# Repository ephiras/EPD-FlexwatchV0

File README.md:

# The Inkwell Watch (A curved eink watch)

previously the flexwatch.

A simple, low stress smartwatch built around a 2.9 inch e ink display, a custom PCB, and a lot of improvised problem solving. This repository contains the Arduino code and the Eagle hardware files for the current working version.

The goal is a comfortable watch that is easy on the eyes, lasts a long time on a charge, and does not behave like a tiny phone.

---

## What is in this repository

### code
Arduino sketches for the current version.  
Bluetooth and microphone support are not implemented yet, but the hardware is ready.

### hardware
Eagle schematic and PCB layout for the custom flex board used in the build.

---

## Current features

- 2.9 inch e ink display  
- Seeed Studio nRF52840 Sense  
- IMU support  
- Basic watch interface  
- Low power modes  
- Custom flex PCB  
- Ruler based rigid frame  

---

## Planned features

- Bluetooth  
- Microphone  
- GPS (new layout needed)  
- Heart rate sensor  
- UV sensor  
- Rigid flex PCB  
- Improved sleep modes  
- RTC backup battery  

---

# The Zephyr Migration
I’ve started migrating the firmware for the e‑ink smartwatch from the Arduino environment to Zephyr RTOS. This is a significant step forward for the project and sets up a much more robust foundation for future development.

## Why the migration
- Better power management: Zephyr gives fine‑grained control over sleep states, peripherals, and scheduling, which is essential for a low‑power wearable running on a small battery.
- Native nRF52840 support: Zephyr’s Nordic integration is far deeper than Arduino’s, with first‑class drivers, BLE stack support, and stable APIs.
- Modular architecture: The RTOS structure makes it easier to separate display handling, sensors, BLE, and UI logic into clean, maintainable modules.
- Scalability: As the watch grows beyond a simple prototype, Arduino’s abstractions become limiting. Zephyr provides a long‑term path for more complex features.

---

## Notes
This is a work in progress.  
The hardware files match the version shown in the Instructables build.  https://www.instructables.com/Building-a-Lightweight-Curved-EInk-Smartwatch/
Expect changes as the design evolves.

if you want to, please join the discord
https://discord.gg/58VtJPHzf

## License

MIT License.  
Feel free to use, modify, and build on this project.

Please reach out or credit me if you do use any of my schematics/ pcb layout. I would really appreciate it! would also be great to see what you come up with.

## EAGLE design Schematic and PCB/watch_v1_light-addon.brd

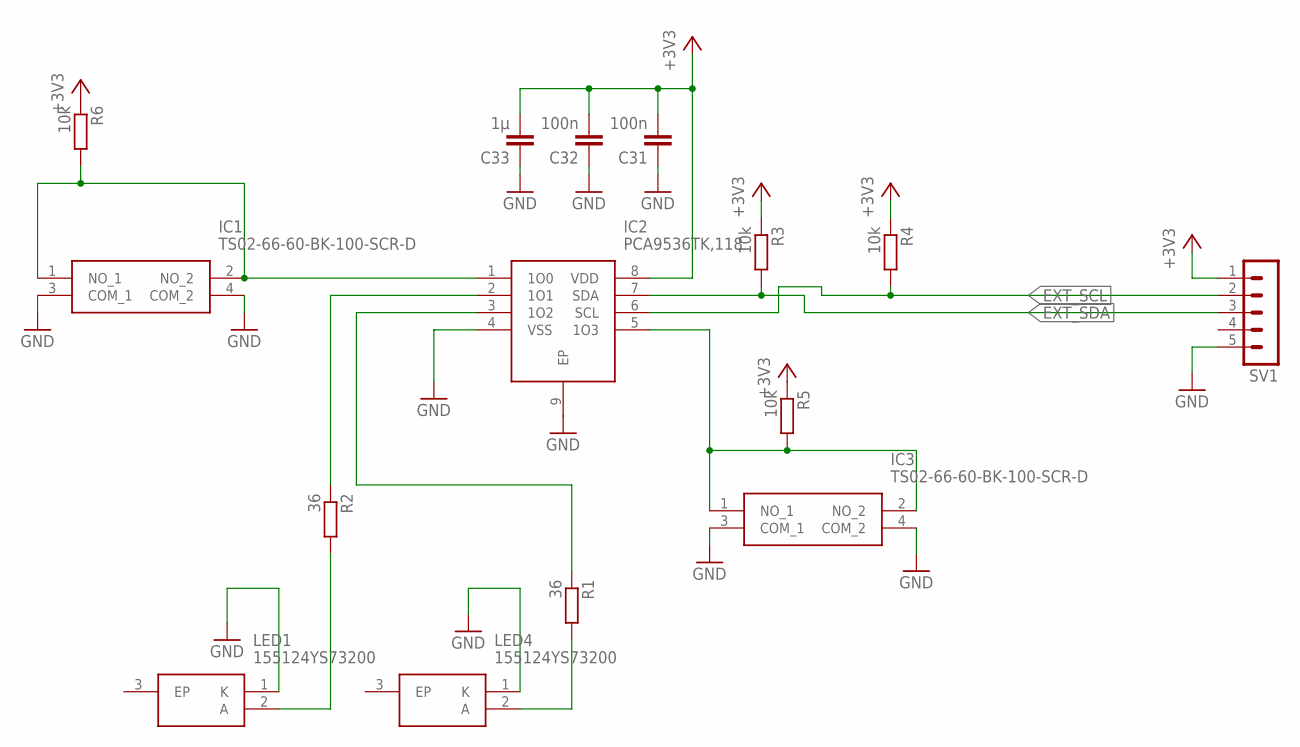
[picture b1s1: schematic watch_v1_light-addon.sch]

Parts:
C31, C32: 100n; C0402_S
C33: 1µ; C0402_S
IC1, IC3: TS02-66-60-BK-100-SCR-D; TS026660BK100SCRD
IC2: PCA9536TK,118; SON50P300X300X100-9N
LED1, LED4: 155124YS73200
R1, R2: 36; R0402
R3, R4, R5, R6: 10k; R0402
SV1: MA05-1

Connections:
+3V3: C31.P$2 (2), C32.P$2 (2), C33.P$2 (2), IC2.8 (VDD), R3.1, R4.1, R5.1, R6.1, SV1.1
EXT_SCL: IC2.6 (SCL), R4.2, SV1.2
EXT_SDA: IC2.7 (SDA), R3.2, SV1.3
GND: C31.P$1 (1), C32.P$1 (1), C33.P$1 (1), IC1.3 (COM_1), IC1.4 (COM_2), IC2.4 (VSS), IC2.9 (EP), IC3.3 (COM_1), IC3.4 (COM_2), LED1.1 (K), LED4.1 (K), SV1.5
unnamed: IC1.1 (NO_1), IC1.2 (NO_2), IC2.1 (1O0), R6.2
unnamed: IC2.2 (1O1), R2.1
unnamed: LED4.2 (A), R1.2
unnamed: LED1.2 (A), R2.2
unnamed: IC2.3 (1O2), R1.1
unnamed: IC2.5 (1O3), IC3.1 (NO_1), IC3.2 (NO_2), R5.2

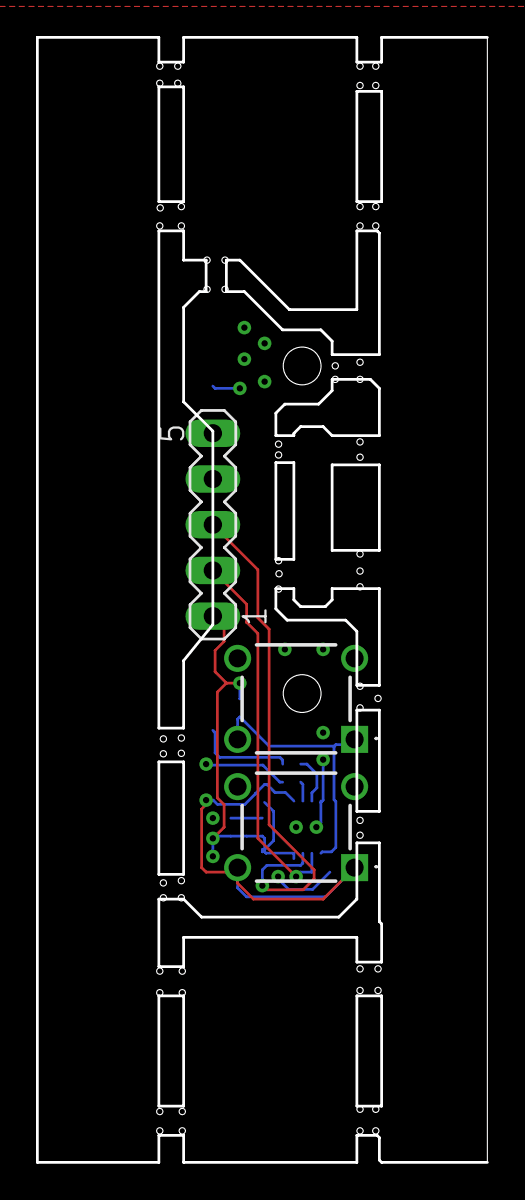
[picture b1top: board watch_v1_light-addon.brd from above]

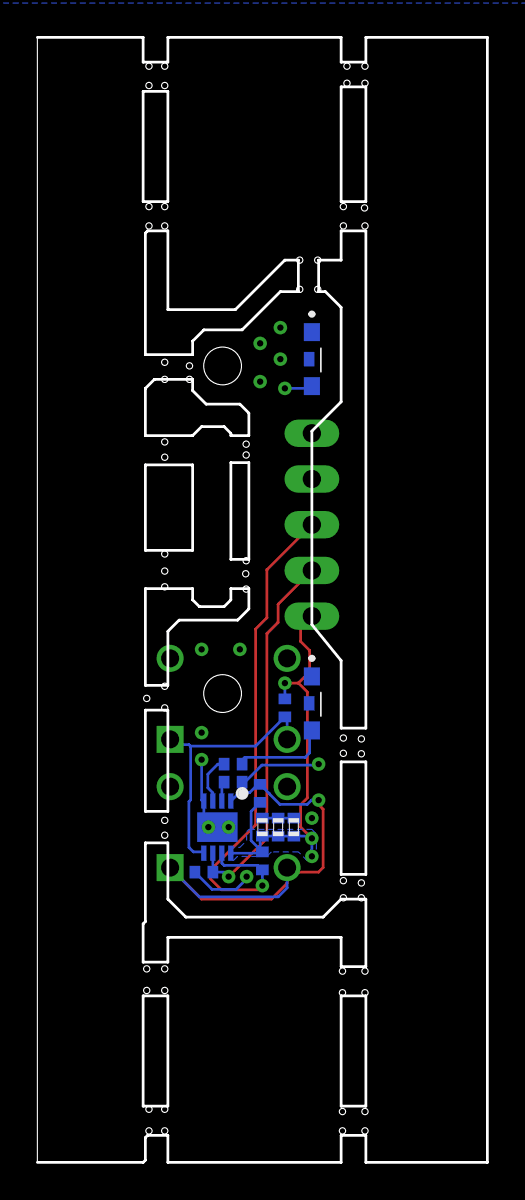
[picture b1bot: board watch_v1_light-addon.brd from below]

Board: 4 copper layers, 25.0 x 62.5 mm, 15 parts (12 on the bottom side), 10 nets.

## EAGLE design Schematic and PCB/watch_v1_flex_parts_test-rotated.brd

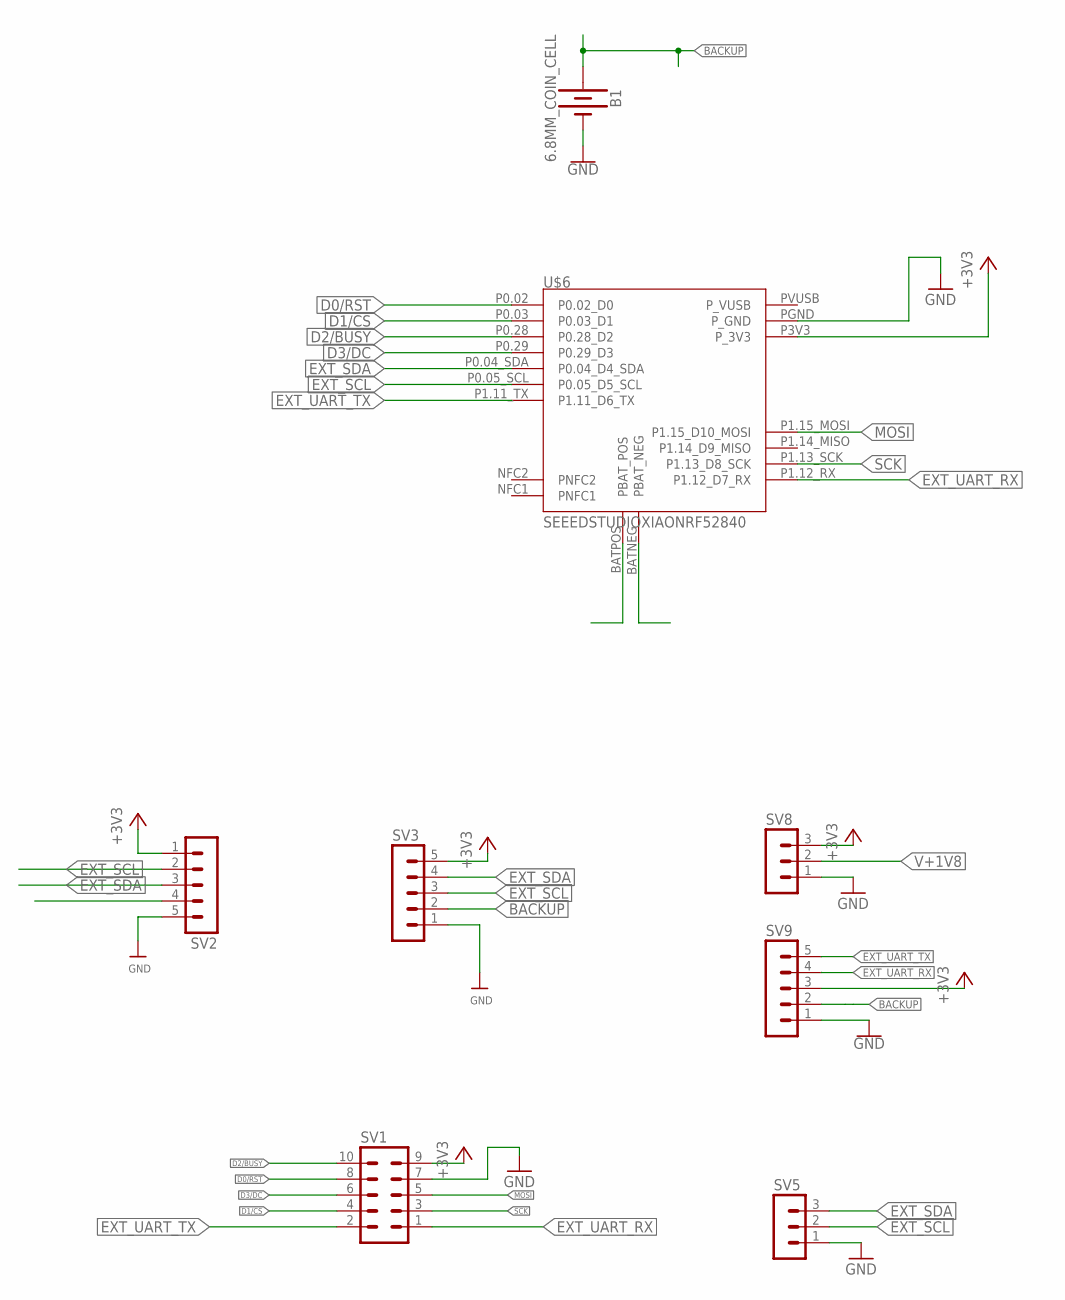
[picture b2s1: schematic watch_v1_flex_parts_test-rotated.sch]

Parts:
B1: 6.8MM_COIN_CELL; ML414H_IV01E
SV1: MA05-2
SV2, SV3, SV9: MA05-1
SV5, SV8: MA03-1
U$6: SEEEDSTUDIOXIAONRF52840

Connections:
+3V3: SV1.9, SV2.1, SV3.5, SV8.3, SV9.3, U$6.P3V3 (P_3V3)
BACKUP: B1.+, SV3.2, SV9.2
D0/RST: SV1.8, U$6.P0.02 (P0.02_D0)
D1/CS: SV1.4, U$6.P0.03 (P0.03_D1)
D2/BUSY: SV1.10, U$6.P0.28 (P0.28_D2)
D3/DC: SV1.6, U$6.P0.29 (P0.29_D3)
EXT_SCL: SV2.2, SV3.3, SV5.2, U$6.P0.05_SCL (P0.05_D5_SCL)
EXT_SDA: SV2.3, SV3.4, SV5.3, U$6.P0.04_SDA (P0.04_D4_SDA)
EXT_UART_RX: SV1.1, SV9.4, U$6.P1.12_RX (P1.12_D7_RX)
EXT_UART_TX: SV1.2, SV9.5, U$6.P1.11_TX (P1.11_D6_TX)
GND: B1.-, SV1.7, SV2.5, SV3.1, SV5.1, SV8.1, SV9.1, U$6.PGND (P_GND)
MOSI: SV1.5, U$6.P1.15_MOSI (P1.15_D10_MOSI)
SCK: SV1.3, U$6.P1.13_SCK (P1.13_D8_SCK)
V+1V8: SV8.2

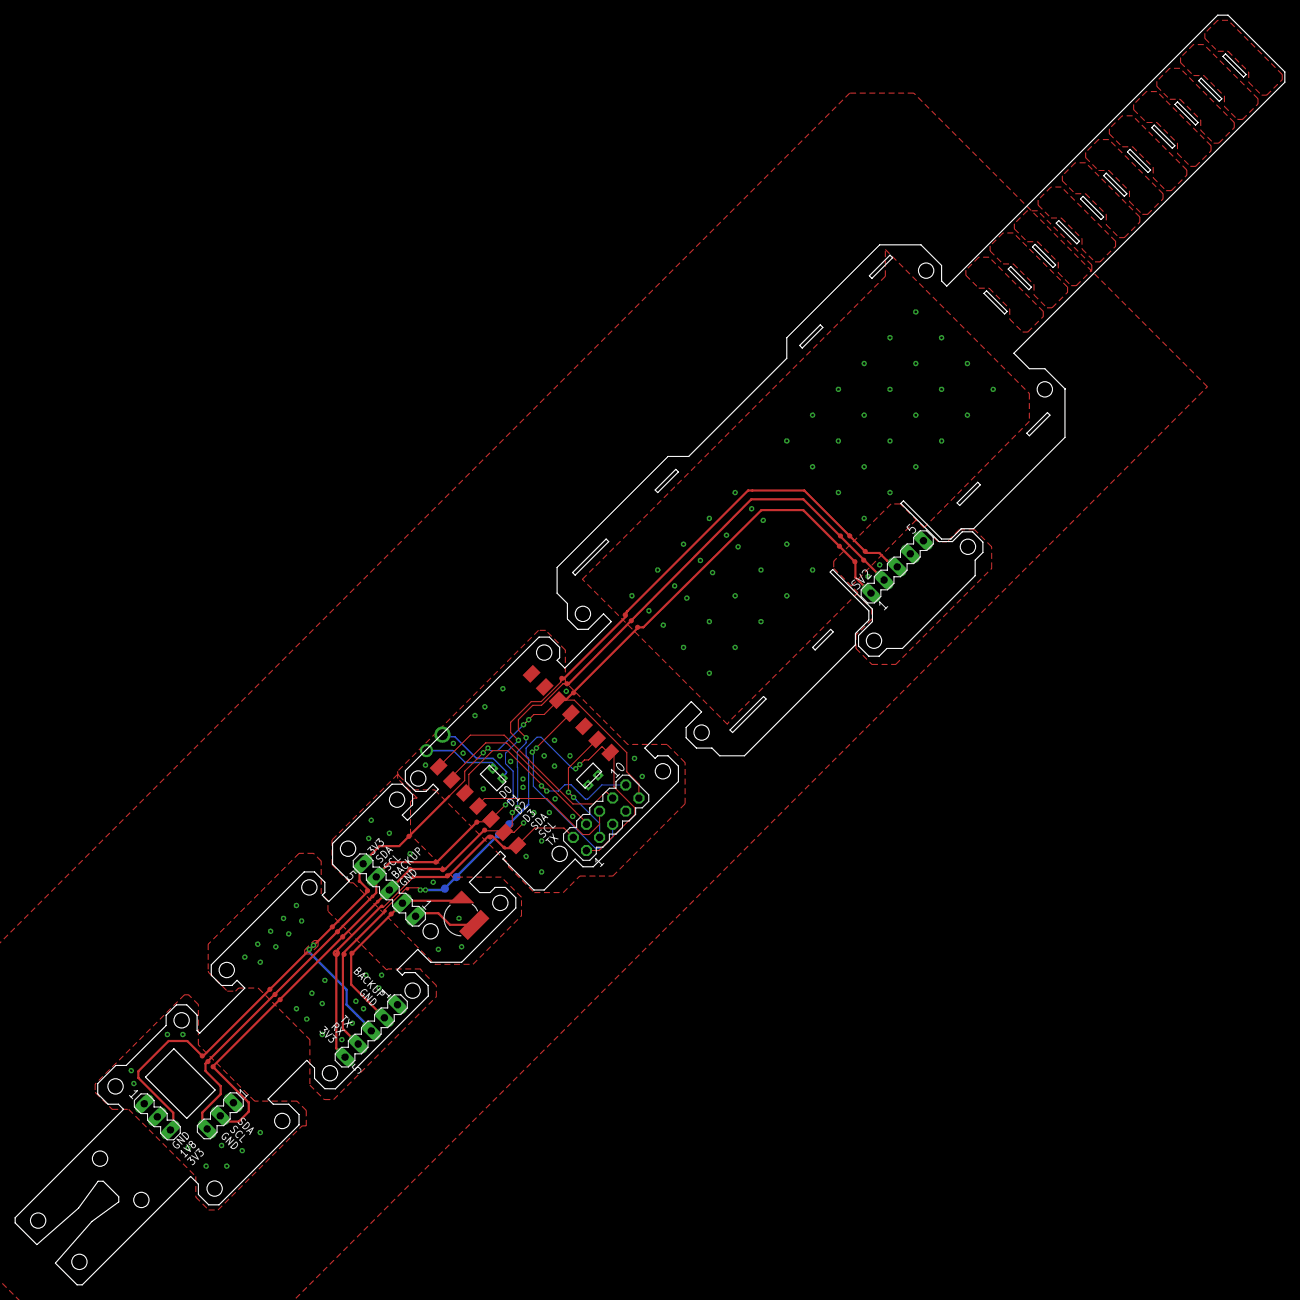
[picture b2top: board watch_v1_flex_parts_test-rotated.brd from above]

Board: 2 copper layers, 173.9 x 173.9 mm, 8 parts (0 on the bottom side), 13 nets.

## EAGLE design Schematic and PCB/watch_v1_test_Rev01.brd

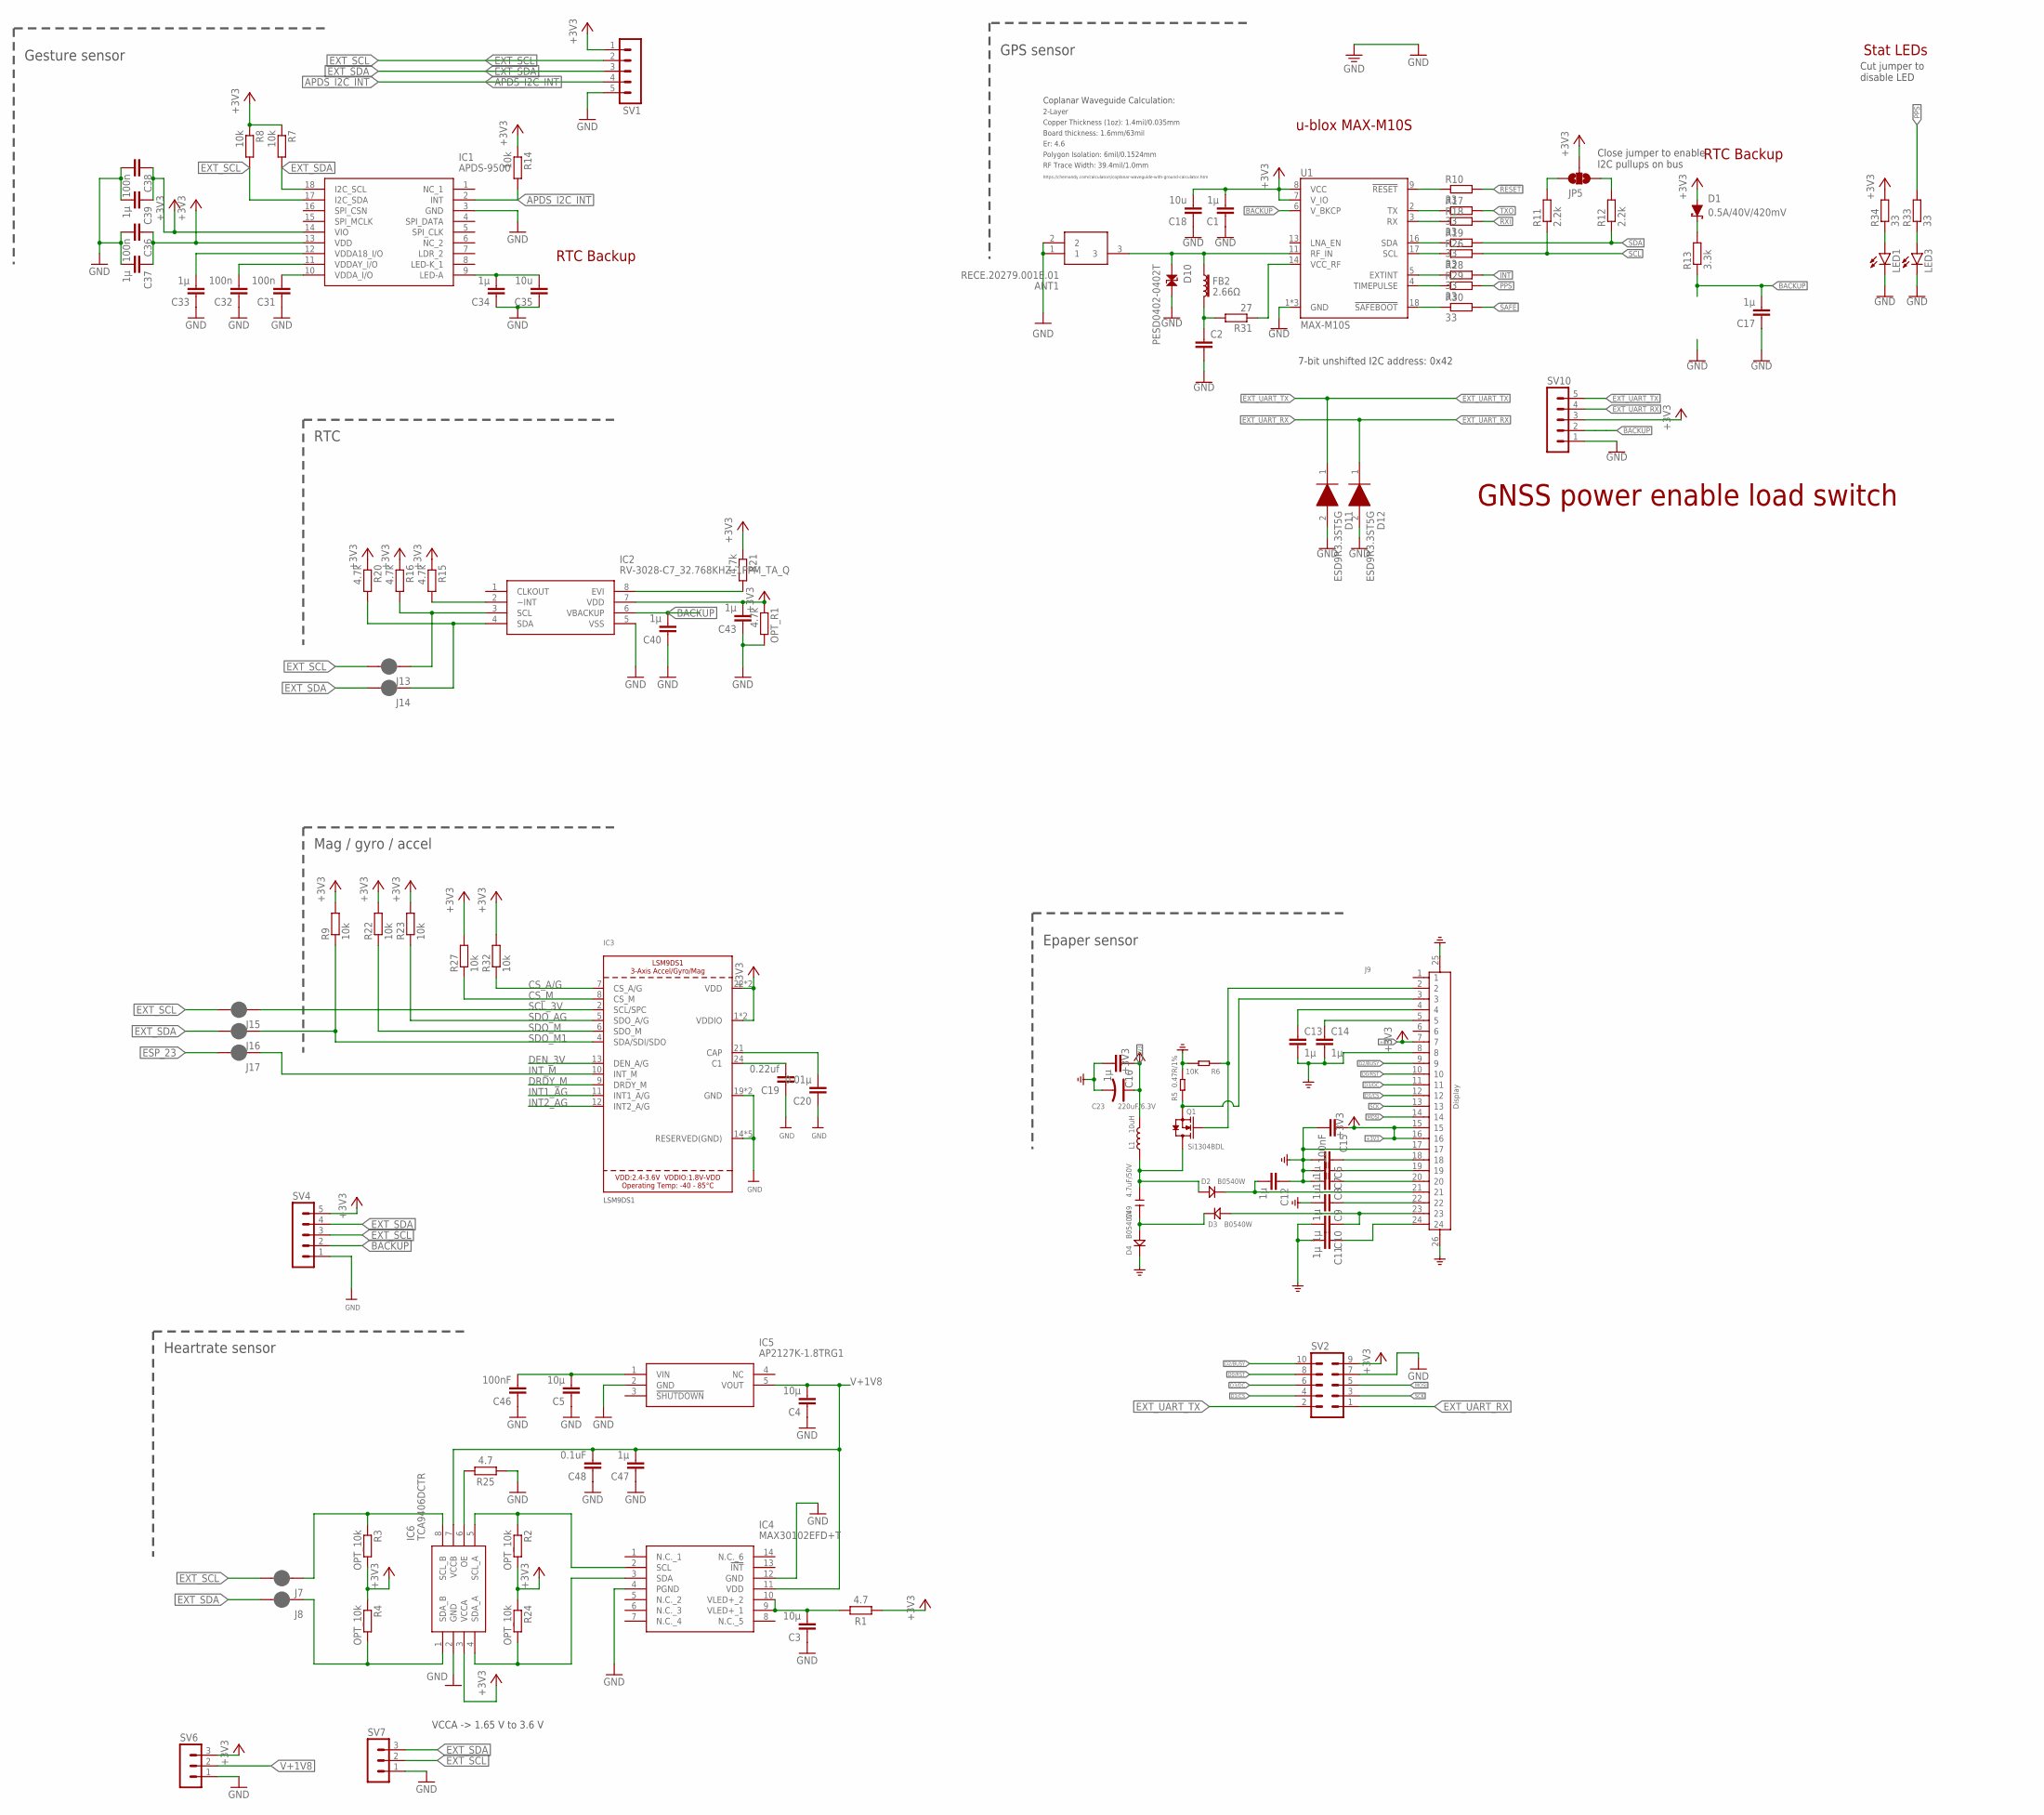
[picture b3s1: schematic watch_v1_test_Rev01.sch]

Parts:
ANT1: RECE.20279.001E.01
C1, C6, C7, C8, C9, C10, C11, C12, C13, C14, C16, C17, C33, C34, C37, C39, C40, C43, C47: 1µ; C0402_S
C2: 47pF; 0402-TIGHT
C3, C4, C5: 10µ; C0402_S
C15, C46: 100nF; C0402_S
C18, C35: 10u; C0402_S
C19: 0.22uf; C0402_S
C20: 0.01µ; C0402_S
C23: 220uF/6.3V; AVX-B
C31, C32, C36, C38: 100n; C0402_S
C48: 0.1uF; C0402_S
C49: 4.7uF/50V; C1206
D1: 0.5A/40V/420mV; SOD-323
D2, D3, D4: B0540W; SOD-323
D10: PESD0402-0402T; 0402-TIGHT
D11, D12: ESD9R3.3ST5G; SODFL1006X40N
FB2: 2.66Ω; 0402-TIGHT
IC1: APDS-9500; APDS9500
IC2: RV-3028-C7_32.768KHZ_1PPM_TA_Q; RV3028C732768KHZ1PPMTAQC
IC3: LSM9DS1; LGA24_3.5X3.1MM
IC4: MAX30102EFD+T; MAX30102EFDT
IC5: AP2127K-1.8TRG1; SOT95P282X145-5N
IC6: TCA9406DCTR; SOP65P400X130-8N
J7, J8, J13, J14, J15, J16, J17: SMT_JUMPER_2_NC_PASTE; JUMPER_SMALL
J9: Display; FPCB24-SMD-0.5-17.6X5.0X2MM
JP5: JUMPER-SMT_3_NO_SILK; SMT-JUMPER_3_NO_SILK
L1: 10uH; L0420
LED1, LED3: LEDSML0603; SML0603; MPN 150060GS84000
OPT_R1: 4.7k; R0402
Q1: Si1304BDL; SOT-323
R1, R25: 4.7; RESC1608X60
R2, R3, R4, R24: OPT_10k; R0402
R5: 0.47R/1%; R0603
R6: 10K; R0603
R7, R8, R9, R14, R22, R23, R27, R32: 10k; R0402
R10, R17, R18, R19, R26, R28, R29, R30, R33, R34: 33; R0402
R11, R12: 2.2k; R0402
R13: 3.3k; R0402
R15, R16, R20, R21: 4.7k; R0402
R31: 27; R0402
SV1, SV4, SV10: MA05-1
SV2: MA05-2
SV6, SV7: MA03-1
U1: MAX-M10S

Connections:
!RESET: R10.2
!SAFE: R30.2
+3V3: C1.P$2 (2), C15.P$1 (1), C16.P$1 (1), C18.P$2 (2), C23.+, C36.P$1 (1), C37.P$1 (1), C38.P$1 (1), C39.P$1 (1), C43.P$2 (2), D1.A, IC1.13 (VDD), IC1.14 (VIO), IC2.7 (VDD), IC3.1 (VDDIO), IC3.3 (VDDIO), IC3.22 (VDD), IC3.23 (VDD), IC6.3 (VCCA), J9.7, J9.15, J9.16, JP5.2, L1.2, OPT_R1.1, R1.1, R2.2, R3.2, R4.1, R7.1, R8.1, R9.2, R14.1, R15.1, R16.1, R20.1, R21.1, R22.2, R23.2, R24.1, R27.2, R32.2, R34.2, SV1.1, SV2.9, SV4.5, SV6.3, SV10.3, U1.7 (V_IO), U1.8 (VCC)
ANT_VCC: C2.1, FB2.2, R31.2
APDS_I2C_INT: IC1.2 (INT), R14.2, SV1.4
BACKUP: C17.P$2 (2), C40.P$2 (2), IC2.6 (VBACKUP), R13.1, SV4.2, SV10.2, U1.6 (V_BKCP)
C1: C19.P$2 (2), IC3.24 (C1)
CAP: C20.P$2 (2), IC3.21 (CAP)
CS_A/G: IC3.7 (CS_A/G), R32.1
CS_M: IC3.8 (CS_M), R27.1
D0/RST: J9.10, SV2.8
D1/CS: J9.12, SV2.4
D2/BUSY: J9.9, SV2.10
D3/DC: J9.11, SV2.6
DEN_3V: IC3.13 (DEN_A/G)
DRDY_M: IC3.9 (DRDY_M)
ESP_23: J17.P$2 (2)
EXTINT_LV: R28.1, U1.5 (EXTINT)
EXT_SCL: IC1.17 (I2C_SDA), J7.P$2 (2), J13.P$2 (2), J15.P$2 (2), R8.2, SV1.2, SV4.3, SV7.2
EXT_SDA: IC1.18 (I2C_SCL), J8.P$2 (2), J14.P$2 (2), J16.P$2 (2), R7.2, SV1.3, SV4.4, SV7.3
EXT_UART_RX: D12.1 (K), SV2.1, SV10.4
EXT_UART_TX: D11.1 (K), SV2.2, SV10.5
GDR: J9.2, Q1.1 (G), R6.1
GND: ANT1.1, ANT1.2, C1.P$1 (1), C2.2, C3.P$1 (1), C4.P$1 (1), C5.P$1 (1), C6.P$2 (2), C7.P$2 (2), C8.P$2 (2), C9.P$2 (2), C10.P$2 (2), C11.P$2 (2), C12.P$1 (1), C13.P$2 (2), C14.P$2 (2), C15.P$2 (2), C16.P$2 (2), C17.P$1 (1), C18.P$1 (1), C19.P$1 (1), C20.P$1 (1), C23.-, C31.P$1 (1), C32.P$1 (1), C33.P$1 (1), C34.P$1 (1), C35.P$1 (1), C36.P$2 (2), C37.P$2 (2), C38.P$2 (2), C39.P$2 (2), C40.P$1 (1), C43.P$1 (1), C46.P$1 (1), C47.P$1 (1), C48.P$1 (1), D4.-, D10.2, D11.2 (A), D12.2 (A), IC1.3 (GND), IC2.5 (VSS), IC3.14 (RESERVED(GND)), IC3.15 (RESERVED(GND)), IC3.16 (RESERVED(GND)), IC3.17 (RESERVED(GND)), IC3.18 (RESERVED(GND)), IC3.19 (GND), IC3.20 (GND), IC4.4 (PGND), IC4.12 (GND), IC5.2 (GND), IC6.2 (GND), J9.8, J9.17, J9.25 (P1), J9.26 (P2), LED1.C, LED3.C, OPT_R1.2, R5.2, R6.2, R25.1, SV1.5, SV2.7, SV4.1, SV6.1, SV7.1, SV10.1, U1.1 (GND), U1.10 (GND), U1.12 (GND)
GPS_RF: ANT1.3, D10.1, FB2.1, U1.11 (RF_IN)
INT: R28.2
INT1_AG: IC3.11 (INT1_A/G)
INT2_AG: IC3.12 (INT2_A/G)
INT_M: IC3.10 (INT_M), J17.P$1 (1)
MOSI: J9.14, SV2.5
unnamed: C5.P$2 (2), C46.P$2 (2), IC5.1 (VIN)
unnamed: IC4.2 (SCL), IC6.5 (SCL_A), R2.1
unnamed: IC4.3 (SDA), IC6.4 (SDA_A), R24.2
unnamed: C31.P$2 (2), IC1.10 (VDDA_I/O)
unnamed: IC6.8 (SCL_B), J7.P$1 (1), R3.1
unnamed: IC6.1 (SDA_B), J8.P$1 (1), R4.2
unnamed: LED3.A, R33.1
unnamed: C32.P$2 (2), IC1.11 (VDDAY_I/O)
unnamed: C33.P$2 (2), IC1.12 (VDDA18_I/O)
unnamed: C34.P$2 (2), C35.P$2 (2), IC1.9 (LED-A)
unnamed: LED1.A, R34.1
unnamed: IC2.4 (SDA), J14.P$1 (1), R20.2
unnamed: C3.P$2 (2), IC4.9 (VLED+_1), IC4.10 (VLED+_2), R1.2
unnamed: IC2.3 (SCL), J13.P$1 (1), R16.2
unnamed: IC2.2 (~INT), R15.2
unnamed: JP5.1, R12.2
unnamed: JP5.3, R11.2
unnamed: D1.C, R13.2
unnamed: C6.P$1 (1), J9.18
unnamed: C7.P$1 (1), J9.19
unnamed: C8.P$1 (1), J9.20
unnamed: IC6.6 (OE), R25.2
unnamed: IC2.8 (EVI), R21.2
unnamed: C12.P$2 (2), D2.-, J9.21
unnamed: C9.P$1 (1), J9.22
unnamed: C10.P$1 (1), D3.+, J9.23
unnamed: C49.1, D3.-, D4.+
unnamed: C49.2, D2.+, L1.1, Q1.3 (D)
unnamed: C13.P$1 (1), J9.4
PPS: R29.2, R33.2
PPS_LV: R29.1, U1.4 (TIMEPULSE)
RESE: J9.3, Q1.2 (S), R5.1
RST_LV: R10.1, U1.9 (!RESET!)
RXI: R18.2
RXLV: R18.1, U1.3 (RX)
SAFE_LV: R30.1, U1.18 (!SAFEBOOT!)
SCK: J9.13, SV2.3
SCL: R11.1, R26.2
SCL_3V: IC3.2 (SCL/SPC), J15.P$1 (1)
SCL_LV: R26.1, U1.17 (SCL)
SDA: R12.1, R19.2
SDA_LV: R19.1, U1.16 (SDA)
SDO_AG: IC3.5 (SDO_A/G), R23.1
SDO_M: IC3.6 (SDO_M), R22.1
SDO_M1: IC3.4 (SDA/SDI/SDO), J16.P$1 (1), R9.1
TXLV: R17.1, U1.2 (TX)
TXO: R17.2
V+1V8: C4.P$2 (2), C47.P$2 (2), C48.P$2 (2), IC4.11 (VDD), IC5.5 (VOUT), IC6.7 (VCCB), SV6.2
VCC_RF: R31.1, U1.14 (VCC_RF)
VCOM: C11.P$1 (1), J9.24
VGH: C14.P$1 (1), J9.5

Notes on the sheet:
VCCA -> 1.65 V to 3.6 V
Heartrate sensor
Mag / gyro / accel
RTC
GNSS power enable load switch
GPS sensor
Epaper sensor
7-bit unshifted I2C address: 0x42
u-blox MAX-M10S
RTC Backup
Close jumper to enable I2C pullups on bus
Coplanar Waveguide Calculation:
Board thickness: 1.6mm/63mil
Er: 4.6
Copper Thickness (1oz): 1.4mil/0.035mm
RF Trace Width: 39.4mil/1.0mm
Polygon Isolation: 6mil/0.1524mm
2-Layer
https://chemandy.com/calculators/coplanar-waveguide-with-ground-calculator.htm
Stat LEDs
Cut jumper to disable LED
Gesture sensor

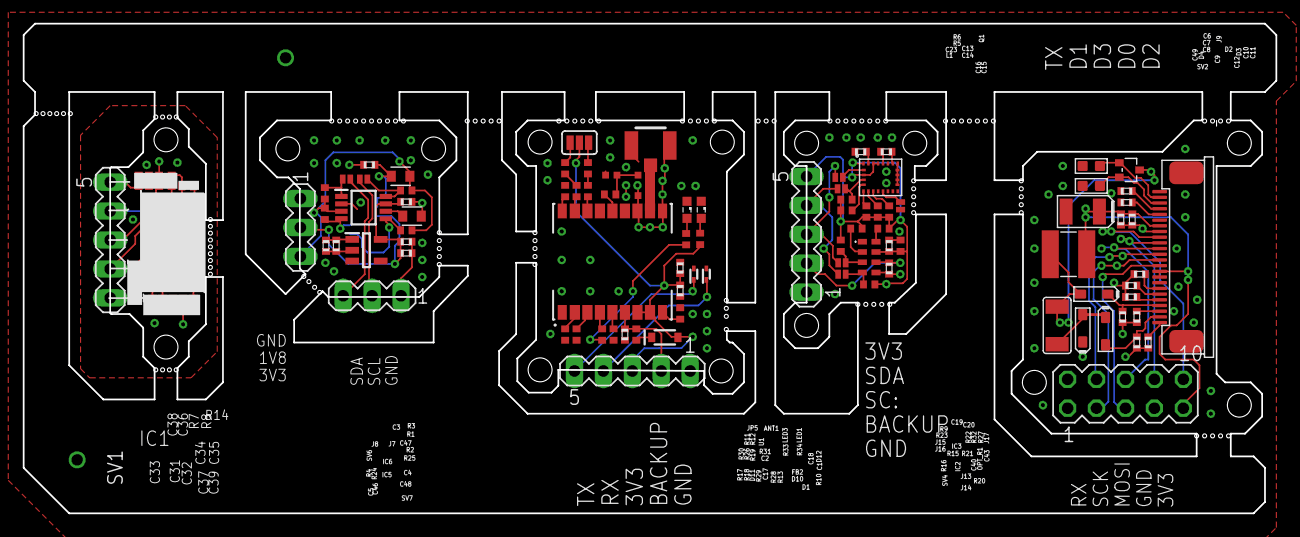
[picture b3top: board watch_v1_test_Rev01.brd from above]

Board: 2 copper layers, 110.0 x 43.0 mm, 106 parts (1 on the bottom side), 71 nets.

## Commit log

2026-03-31 Added .Sch and PCB files

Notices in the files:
parts and their libraries:
SparkFun-Batteries: Licensing: Creative Commons ShareAlike 4.0 International - https://creativecommons.org/licenses/by-sa/4.0
microbuilder: This work is placed in the public domain, and may be freely used for commercial and non-commercial work with the following conditions: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
